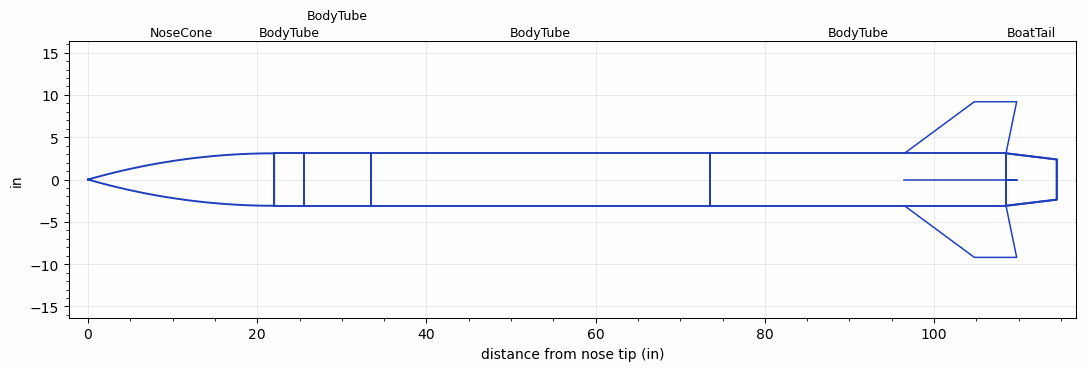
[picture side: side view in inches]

<RASAeroDocument>
 <FileVersion>2</FileVersion>
 <RocketDesign>
  <NoseCone>
   <Length>22</Length>
   <Diameter>6.2</Diameter>
   <Shape>Tangent Ogive</Shape>
   <Location>0</Location>
  </NoseCone>
  <BodyTube>
   <Length>3.5</Length>
   <Diameter>6.2</Diameter>
   <Location>22</Location>
  </BodyTube>
  <BodyTube>
   <Length>8</Length>
   <Diameter>6.2</Diameter>
   <Location>25.4999</Location>
  </BodyTube>
  <BodyTube>
   <Length>39.9999</Length>
   <Diameter>6.2</Diameter>
   <RailGuideDiameter>0.3819</RailGuideDiameter>
   <RailGuideHeight>0.3819</RailGuideHeight>
   <Location>33.4999</Location>
  </BodyTube>
  <BodyTube>
   <Length>34.9999</Length>
   <Diameter>6.2</Diameter>
   <RailGuideDiameter>0.3819</RailGuideDiameter>
   <RailGuideHeight>0.3819</RailGuideHeight>
   <Location>73.4999</Location>
   <BoattailLength>6</BoattailLength>
   <BoattailRearDiameter>4.75</BoattailRearDiameter>
   <Fin>
    <Count>4</Count>
    <Chord>12</Chord>
    <Span>6.1</Span>
    <SweepDistance>8.2583</SweepDistance>
    <TipChord>5</TipChord>
    <Thickness>0.1875</Thickness>
    <Location>12</Location>
    <AirfoilSection>Rounded</AirfoilSection>
   </Fin>
  </BodyTube>
  <BoatTail>
   <Length>6</Length>
   <Diameter>6.2</Diameter>
   <RearDiameter>4.75</RearDiameter>
   <Location>108.4998</Location>
  </BoatTail>
  <Surface>Rough Camouflage Paint</Surface>
  <ModifiedBarrowman>False</ModifiedBarrowman>
  <Turbulence>False</Turbulence>
  <UseBooster1>False</UseBooster1>
  <UseBooster2>False</UseBooster2>
 </RocketDesign>
 <LaunchSite>
  <Altitude>4995</Altitude>
  <Pressure>24.9</Pressure>
  <RodAngle>5</RodAngle>
  <RodLength>145</RodLength>
  <Temperature>41.19</Temperature>
  <WindSpeed>0</WindSpeed>
 </LaunchSite>
 <Recovery>
  <Altitude1>1000</Altitude1>
  <Altitude2>0</Altitude2>
  <DeviceType1>Parachute</DeviceType1>
  <DeviceType2>None</DeviceType2>
  <Event1>True</Event1>
  <Event2>False</Event2>
  <Size1>143.9997</Size1>
  <Size2>0</Size2>
  <EventType1>Altitude</EventType1>
  <EventType2>None</EventType2>
  <CD1>0.97</CD1>
  <CD2>0</CD2>
 </Recovery>
 <SimulationList>
  <Simulation>
   <SustainerLaunchWt>63.2303</SustainerLaunchWt>
   <SustainerCG>72.2734</SustainerCG>
   <SustainerIgnitionDelay>0</SustainerIgnitionDelay>
   <Booster1SeparationDelay>0</Booster1SeparationDelay>
   <Booster1IgnitionDelay>0</Booster1IgnitionDelay>
   <IncludeBooster1>False</IncludeBooster1>
   <Booster2Delay>0</Booster2Delay>
   <IncludeBooster2>False</IncludeBooster2>
  </Simulation>
  <Simulation>
   <SustainerLaunchWt>63.2303</SustainerLaunchWt>
   <SustainerCG>72.2734</SustainerCG>
   <SustainerIgnitionDelay>0</SustainerIgnitionDelay>
   <Booster1SeparationDelay>0</Booster1SeparationDelay>
   <Booster1IgnitionDelay>0</Booster1IgnitionDelay>
   <IncludeBooster1>False</IncludeBooster1>
   <Booster2Delay>0</Booster2Delay>
   <IncludeBooster2>False</IncludeBooster2>
  </Simulation>
  <Simulation>
   <SustainerLaunchWt>63.2303</SustainerLaunchWt>
   <SustainerCG>72.2734</SustainerCG>
   <SustainerIgnitionDelay>0</SustainerIgnitionDelay>
   <Booster1SeparationDelay>0</Booster1SeparationDelay>
   <Booster1IgnitionDelay>0</Booster1IgnitionDelay>
   <IncludeBooster1>False</IncludeBooster1>
   <Booster2Delay>0</Booster2Delay>
   <IncludeBooster2>False</IncludeBooster2>
  </Simulation>
  <Simulation>
   <SustainerLaunchWt>63.2303</SustainerLaunchWt>
   <SustainerCG>72.2734</SustainerCG>
   <SustainerIgnitionDelay>0</SustainerIgnitionDelay>
   <Booster1SeparationDelay>0</Booster1SeparationDelay>
   <Booster1IgnitionDelay>0</Booster1IgnitionDelay>
   <IncludeBooster1>False</IncludeBooster1>
   <Booster2Delay>0</Booster2Delay>
   <IncludeBooster2>False</IncludeBooster2>
  </Simulation>
  <Simulation>
   <SustainerLaunchWt>63.2303</SustainerLaunchWt>
   <SustainerCG>72.2734</SustainerCG>
   <SustainerIgnitionDelay>0</SustainerIgnitionDelay>
   <Booster1SeparationDelay>0</Booster1SeparationDelay>
   <Booster1IgnitionDelay>0</Booster1IgnitionDelay>
   <IncludeBooster1>False</IncludeBooster1>
   <Booster2Delay>0</Booster2Delay>
   <IncludeBooster2>False</IncludeBooster2>
  </Simulation>
  <Simulation>
   <SustainerEngine>M2500T  (AT)</SustainerEngine>
   <SustainerLaunchWt>63.13</SustainerLaunchWt>
   <SustainerCG>71.96</SustainerCG>
   <SustainerIgnitionDelay>0</SustainerIgnitionDelay>
   <Booster1SeparationDelay>0</Booster1SeparationDelay>
   <Booster1IgnitionDelay>0</Booster1IgnitionDelay>
   <IncludeBooster1>False</IncludeBooster1>
   <Booster2Delay>0</Booster2Delay>
   <IncludeBooster2>False</IncludeBooster2>
   <TimetoApogee>27.81054</TimetoApogee>
   <MaxAltitude>12483.49</MaxAltitude>
   <MaxVelocity>1008.961</MaxVelocity>
  </Simulation>
 </SimulationList>
</RASAeroDocument>
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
